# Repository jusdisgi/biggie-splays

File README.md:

# biggie-splays
A bigger split keyboard with stagger and splay, for those who want too many keys.

Currently I have completed designs for Choc v1 and v2. I have not tested it but I intend to order PCBs of the v2 design soon. I don't know if I will revisit this one for other switch types. Probably would be a cool MX board though...

I will eventually be working up a case for this one, unlike my previous designs which have all been caseless. Stay tuned!

Please note I have hacked up a couple of the ergogen footprints. In particular the XIAO one has the underside pads that I'm not using removed and replaced with silkscreen drawings. Because that's just a layer change they're easy to put back, either by editing the footprint or manually in KiCad. There's also a reverse-polarity version of the JST connector in the footprints dir, but I ended up not using it.

I am still really new at all of this! Feedback and suggestions are highly encouraged!

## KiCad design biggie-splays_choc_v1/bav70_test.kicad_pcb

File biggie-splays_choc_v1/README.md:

# biggie-splays
The .pcb files that matter are the "left" and "right" ones; the one without a direction in the name is blank.

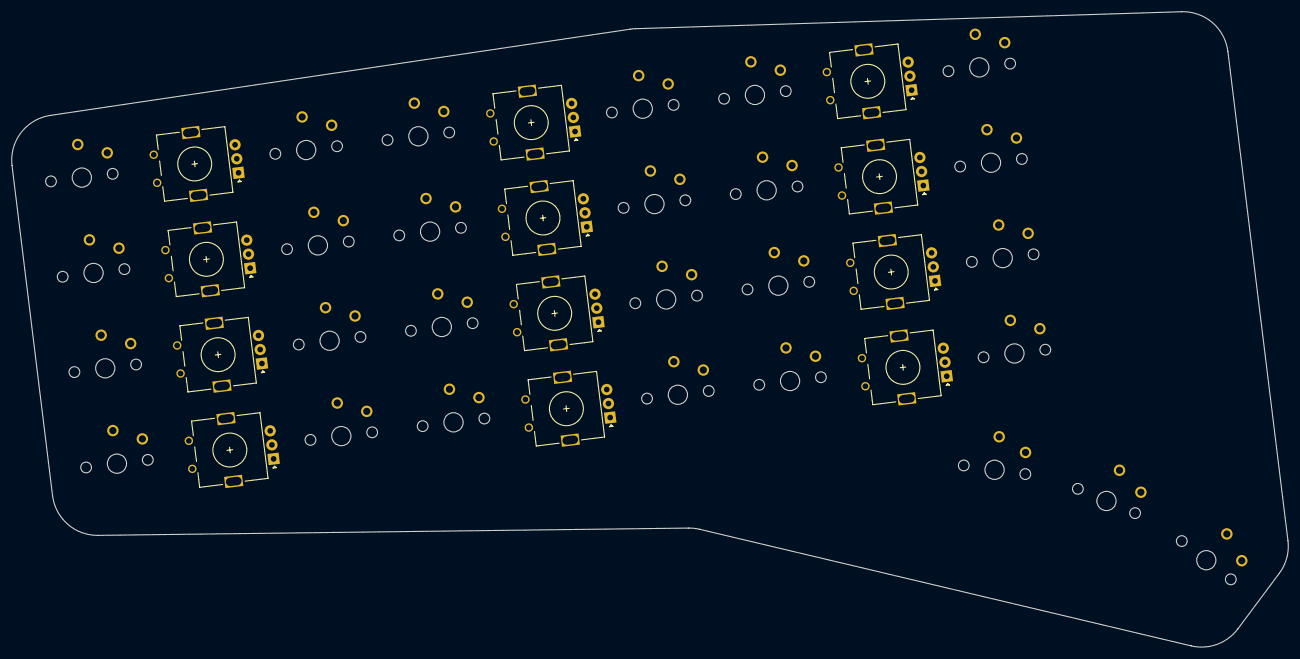
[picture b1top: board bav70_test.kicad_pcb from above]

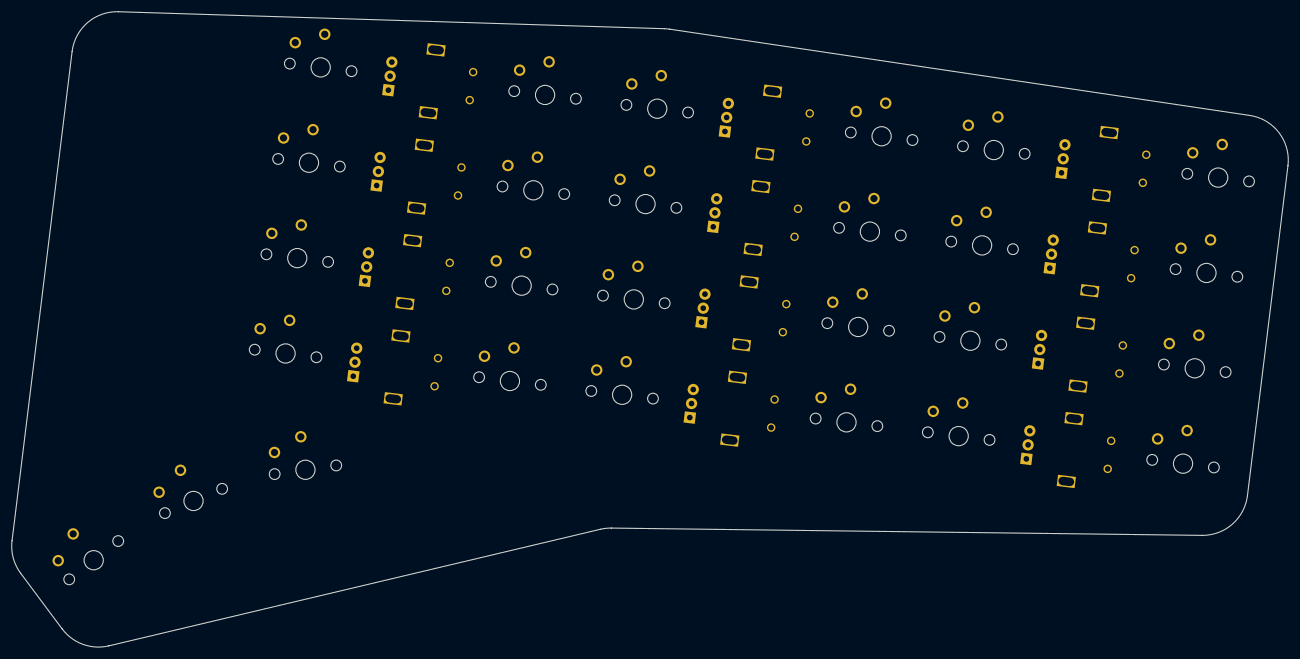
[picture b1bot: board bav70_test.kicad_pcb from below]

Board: 2 copper layers, 225.9 x 112.4 mm, 39 parts (27 on the bottom side), 36 nets, no tracks yet.

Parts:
ROT1, ROT2, ROT3, ROT4, ROT5, ROT6, ROT7, ROT8, ROT9, ROT10, ROT11, ROT12: rotary_encoder
S1, S2, S3, S4, S5, S6, S7, S8, S9, S10, S11, S12, S13, S14, S15, S16, S17, S18, S19, S20, S21, S22, S23, S24, S25, S26, S27: switch_choc_v1_v2

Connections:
Bar: ROT1.C, ROT2.C, ROT3.C, ROT4.C, ROT5.C, ROT6.C, ROT7.C, ROT8.C, ROT9.C, ROT10.C, ROT11.C, ROT12.C
D0: ROT4.2, ROT8.2, ROT12.2
D1: S9.2, S10.2, S11.2, S12.2
D2: ROT3.2, ROT7.2, ROT11.2
D3: S5.2, S6.2, S7.2, S8.2
D4: ROT2.2, ROT6.2, ROT10.2
D5: S1.2, S2.2, S3.2, S4.2
D6: ROT1.2, ROT5.2, ROT9.2
D7: S13.2, S14.2, S15.2, S16.2, S25.2
D8: S17.2, S18.2, S19.2, S20.2, S26.2
D10: S21.2, S22.2, S23.2, S24.2, S27.2
Foo: ROT1.B, ROT2.B, ROT3.B, ROT4.B, ROT5.B, ROT6.B, ROT7.B, ROT8.B, ROT9.B, ROT10.B, ROT11.B, ROT12.B
index_bottom: ROT9.1, S17.1
index_high: ROT11.1, S19.1
index_home: ROT10.1, S18.1
index_num: ROT12.1, S20.1
inner_bottom: ROT9.A, S21.1
inner_high: ROT11.A, S23.1
inner_home: ROT10.A, S22.1
inner_num: ROT12.A, S24.1
middle_bottom: ROT5.A, S13.1
middle_high: ROT7.A, S15.1
middle_home: ROT6.A, S14.1
middle_num: ROT8.A, S16.1
pinky_bottom: ROT1.A, S5.1
pinky_high: ROT3.A, S7.1
pinky_home: ROT2.A, S6.1
pinky_num: ROT4.A, S8.1
ring_bottom: ROT5.1, S9.1
ring_high: ROT7.1, S11.1
ring_home: ROT6.1, S10.1
ring_num: ROT8.1, S12.1
stretch_bottom: ROT1.1, S1.1
stretch_high: ROT3.1, S3.1
stretch_home: ROT2.1, S2.1
stretch_num: ROT4.1, S4.1

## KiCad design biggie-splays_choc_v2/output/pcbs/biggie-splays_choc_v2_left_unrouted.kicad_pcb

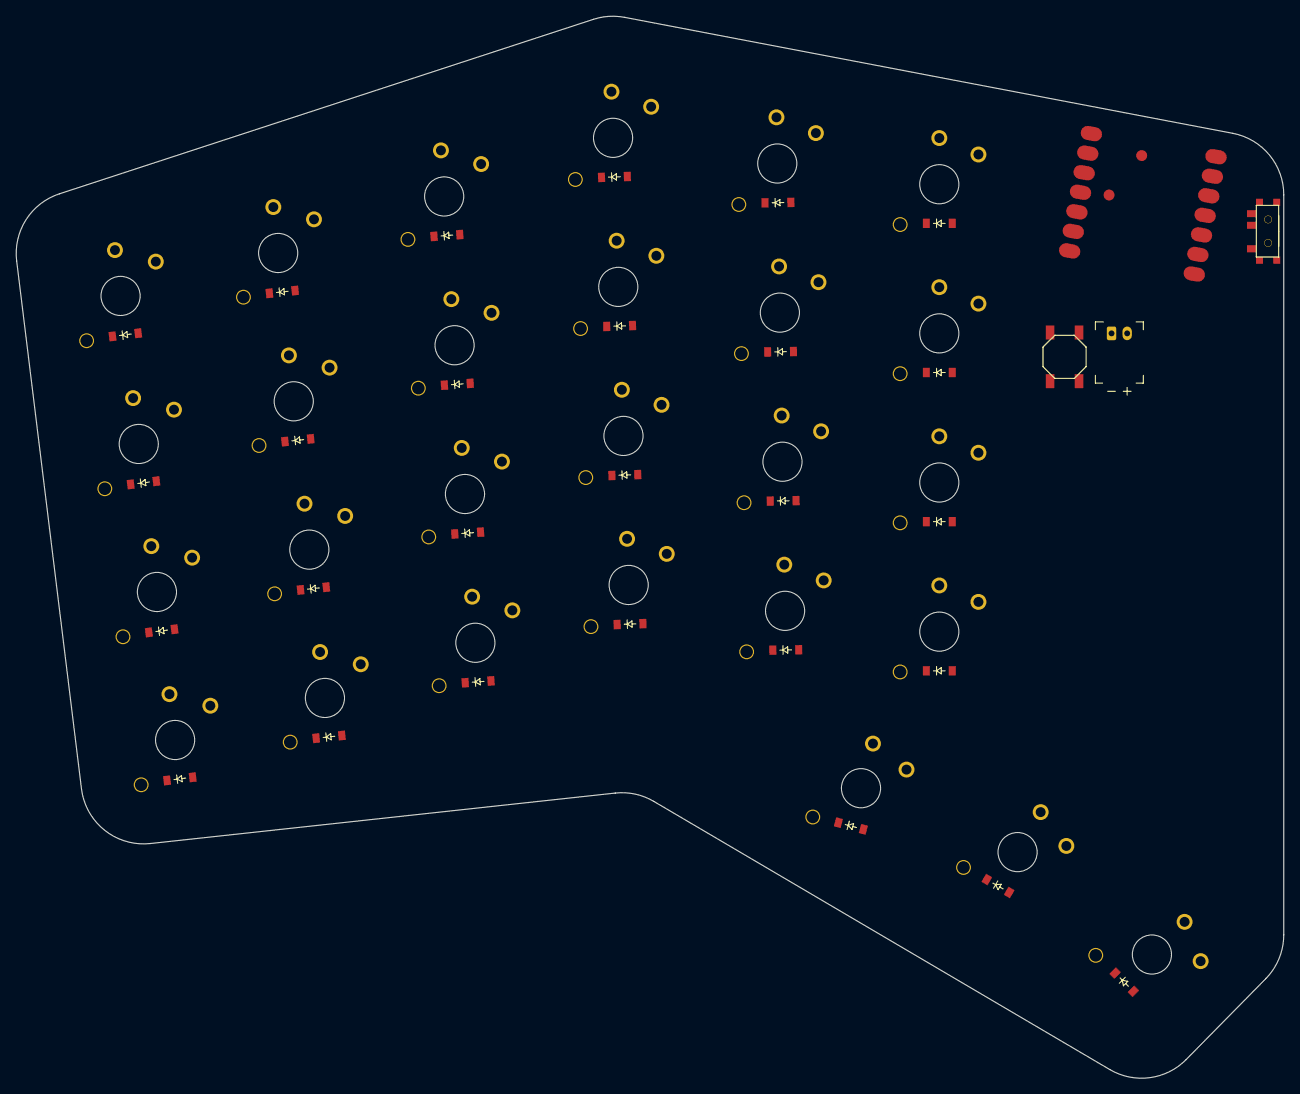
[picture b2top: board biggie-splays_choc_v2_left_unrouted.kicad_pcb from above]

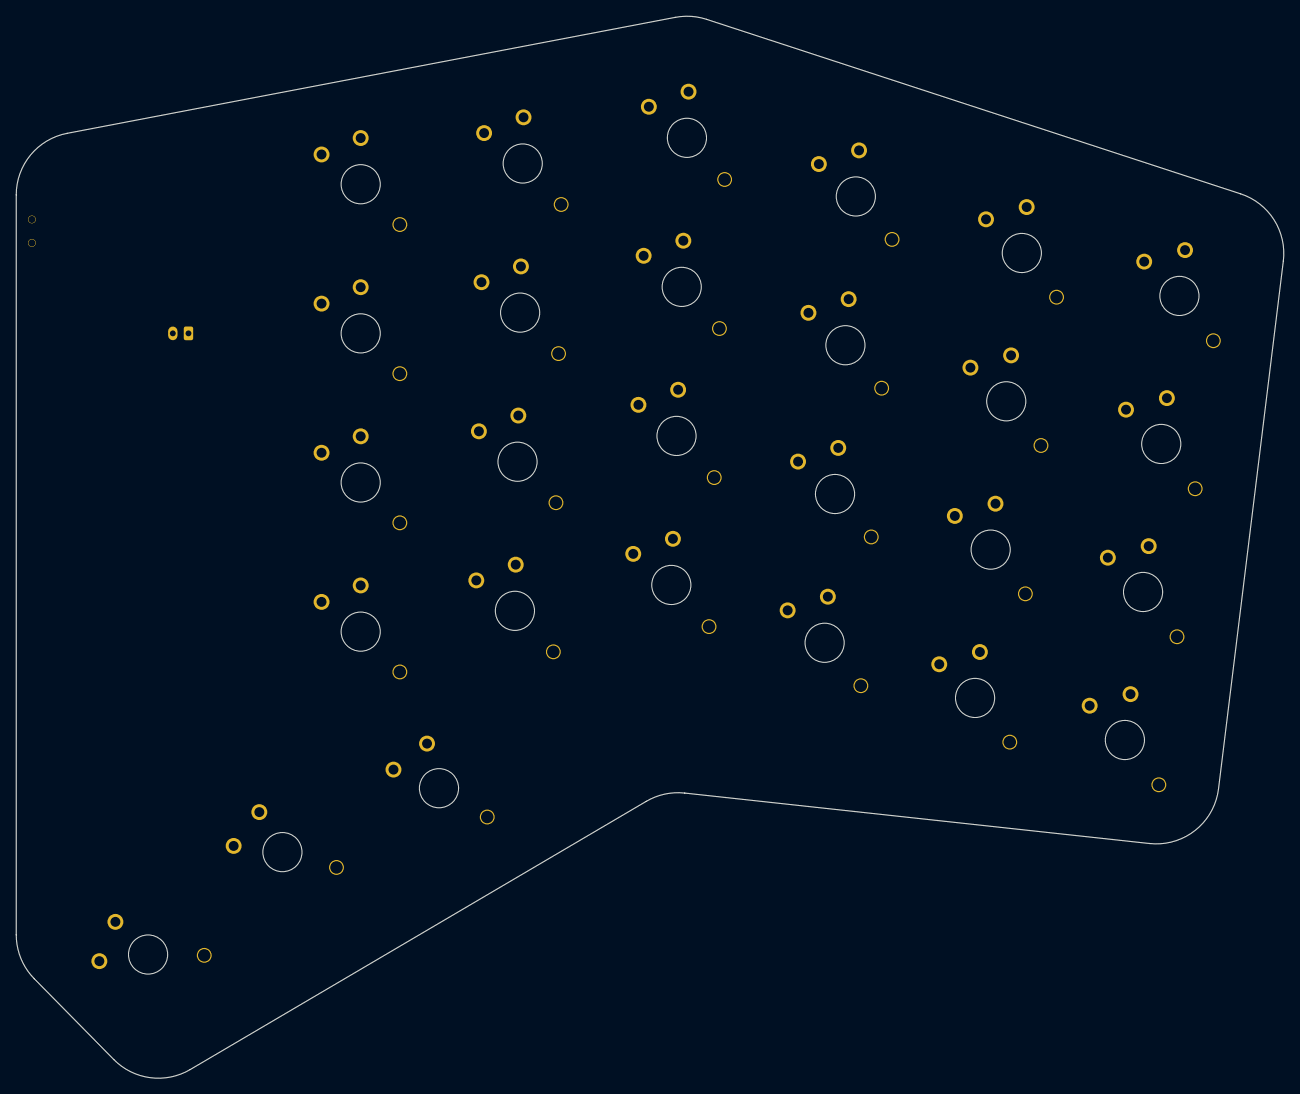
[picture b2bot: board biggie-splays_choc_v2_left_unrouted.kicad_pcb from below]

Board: 2 copper layers, 161.9 x 135.6 mm, 58 parts (27 on the bottom side), 42 nets, no tracks yet.

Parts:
B1: SW_TACT_ALPS_SKQGABE010
D1, D2, D3, D4, D5, D6, D7, D8, D9, D10, D11, D12, D13, D14, D15, D16, D17, D18, D19, D20, D21, D22, D23, D24, D25, D26, D27: diode_tht_sod123
JST1: battery_connector_jst_ph_2
MCU1: xiao_smd
S1, S2, S3, S4, S5, S6, S7, S8, S9, S10, S11, S12, S13, S14, S15, S16, S17, S18, S19, S20, S21, S22, S23, S24, S25, S26, S27: switch_choc_v1_v2
T1: SPDT_C128955

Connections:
BAT: MCU1.19, T1.2
BATCON: JST1.2, T1.1
D0: D4.1, D8.1, D12.1, D16.1, D20.1, D24.1, MCU1.1
D1: MCU1.2, S9.2, S10.2, S11.2, S12.2
D2: D3.1, D7.1, D11.1, D15.1, D19.1, D23.1, MCU1.3
D3: MCU1.4, S5.2, S6.2, S7.2, S8.2
D4: D2.1, D6.1, D10.1, D14.1, D18.1, D22.1, MCU1.5
D5: MCU1.6, S1.2, S2.2, S3.2, S4.2
D6: D1.1, D5.1, D9.1, D13.1, D17.1, D21.1, MCU1.7
D7: MCU1.8, S13.2, S14.2, S15.2, S16.2, S25.2
D8: MCU1.9, S17.2, S18.2, S19.2, S20.2, S26.2
D9: D25.1, D26.1, D27.1, MCU1.10
D10: MCU1.11, S21.2, S22.2, S23.2, S24.2, S27.2
GND: B1.1, JST1.1, MCU1.13, MCU1.18, MCU1.20
RST: B1.2, MCU1.17
far_fan: D27.2, S27.1
index_bottom: D17.2, S17.1
index_high: D19.2, S19.1
index_home: D18.2, S18.1
index_num: D20.2, S20.1
inner_bottom: D21.2, S21.1
inner_high: D23.2, S23.1
inner_home: D22.2, S22.1
inner_num: D24.2, S24.1
mid_fan: D26.2, S26.1
middle_bottom: D13.2, S13.1
middle_high: D15.2, S15.1
middle_home: D14.2, S14.1
middle_num: D16.2, S16.1
near_fan: D25.2, S25.1
pinky_bottom: D5.2, S5.1
pinky_high: D7.2, S7.1
pinky_home: D6.2, S6.1
pinky_num: D8.2, S8.1
ring_bottom: D9.2, S9.1
ring_high: D11.2, S11.1
ring_home: D10.2, S10.1
ring_num: D12.2, S12.1
stretch_bottom: D1.2, S1.1
stretch_high: D3.2, S3.1
stretch_home: D2.2, S2.1
stretch_num: D4.2, S4.1

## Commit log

2025-04-15 Add finished choc v1 project, including ergogen config/footprints, KiCad schematic/PCB files, and production Gerber .zip bundles.
2025-04-17 Create Choc v2 variant, including ergogen config/footprints, schematic, PCB files, and Gerber production files.
2025-04-18 Minor cleanup of unused files
